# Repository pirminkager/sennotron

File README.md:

# sennotron-beeromat

Sennotron is also a great beer brewer!

Read out adc is working
Data collection and saving (data.py) is working

## Installation

It is important to always have a stable and predictive environment. Packages installed on the system
could interfere with packages installed for this project. In addition it makes it easier to install this project
on different systems.

    # create a virtual python environment based on python3.
    # all packages installed with pip will be installed under this location
    virtualenv --python=python3 .venv3

    # apply/source the environment
    # this command needs to be repeated whenever a new shell is opened
    source .venv3/bin/python

    # install project dependencies
    pip install -r requirements.txt

## Todo

### main.py + controls
### mpc.py
### model.py
### error estimation?
### alert.py?
### display.py

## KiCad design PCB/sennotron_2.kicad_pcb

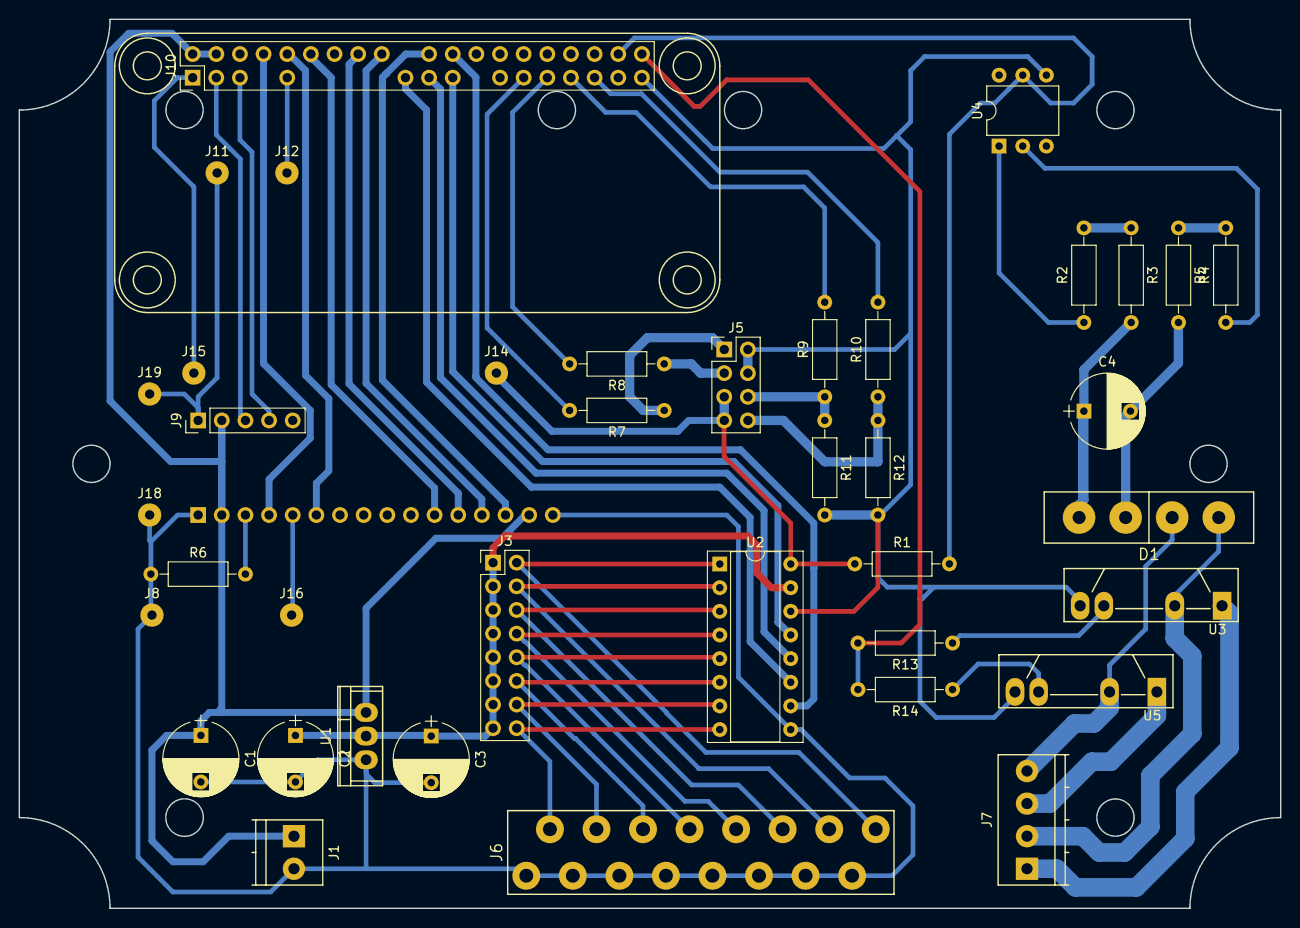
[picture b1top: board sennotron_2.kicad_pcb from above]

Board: 4 copper layers, 135.5 x 95.5 mm, 40 parts (1 on the bottom side), 47 nets.

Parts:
C1, C3: CP; CP_Radial_D8.0mm_P5.00mm
C2: 22µF/50V; CP_Radial_D8.0mm_P5.00mm
C4: C; CP_Radial_D8.0mm_P5.00mm
D1: D_Bridge_+-AA; SIP-4
J1: Screw_Terminal_01x02; TerminalBlock_Phoenix_PT-3.5mm_2pol
J3: Conn_02x08_Odd_Even; Pin_Header_Straight_2x08_Pitch2.54mm
J4: Conn_01x16_Female; Pin_Header_Straight_1x16_Pitch2.54mm
J5: Conn_02x04_Odd_Even; Pin_Header_Straight_2x04_Pitch2.54mm
J6: Screw_Terminal_01x16; springlock
J7: Screw_Terminal_01x04; TerminalBlock_Phoenix_PT-3.5mm_4pol
J8, J11, J12, J14, J15, J16, J18, J19: Conn_01x01; Pad_2.5
J9: Conn_01x05_Female; Socket_Strip_Straight_1x05_Pitch2.54mm
J10: Conn_02x20_Odd_Even; raspberry_pi_zero
R1, R2, R3, R4, R5, R6, R7, R8, R9, R10, R11, R12, R13, R14: R; R_Axial_DIN0207_L6.3mm_D2.5mm_P10.16mm_Horizontal
U1: LM1117-3.3; TO-220
U2: MCP3208; DIP-16_W7.62mm_Socket
U3, U5: S102S01; SIP4_Sharp-SSR_Pitch7.62mm_Straight
U4: 4N28; DIP-6_W7.62mm

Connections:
+3.3VA: C2.1, C3.1, J3.1, J3.3, J3.5, J3.7, J3.9, J3.11, J3.13, J3.15, U1.2, U2.15
+3V3: J5.5, J5.7, J10.1, J14.1, J15.1, R1.1, U2.16
+5V: C1.1, J1.1, J4.2, J4.15, J9.2, J10.2, J10.4, U1.3
/btn1: J10.33, R9.2
/btn2: J10.35, R10.2
/led1: J10.29, R7.2
/led2: J10.31, R8.2
AC_sens: J10.38, R1.2, U4.5
GND: C1.2, C2.2, C3.2, J1.2, J4.1, J4.5, J4.16, J5.2, J5.4, J6.1, J6.3, J6.5, J6.7, J6.9, J6.11, J6.13, J6.15, J8.1, J9.1, J10.9, J10.39, J11.1, J12.1, J16.1, J18.1, J19.1, R6.1, R11.2, R12.2, U1.1, U2.9, U2.14, U3.4, U4.4, U5.4
unnamed: C4.1, D1.1, R3.2
unnamed: C4.2, D1.2, R5.2
unnamed: D1.3, J7.4, U5.2
unnamed: D1.4, J7.2, U3.2
unnamed: J3.2, J6.16, U2.1
unnamed: J3.4, J6.14, U2.2
unnamed: J3.6, J6.12, U2.3
unnamed: J3.8, J6.10, U2.4
unnamed: J3.10, J6.8, U2.5
unnamed: J3.12, J6.6, U2.6
unnamed: J3.14, J6.4, U2.7
unnamed: J3.16, J6.2, U2.8
unnamed: J4.3, R6.2
unnamed: J5.1, R7.1
unnamed: J5.3, R8.1
unnamed: J5.6, R9.1, R11.1
unnamed: J5.8, R10.1, R12.1
unnamed: J7.1, U3.1
unnamed: J7.3, U5.1
unnamed: R2.1, U4.1
unnamed: R2.2, R3.1
unnamed: R4.1, U4.2
unnamed: R4.2, R5.1
unnamed: R13.1, U3.3
unnamed: R14.1, U5.3
heat_trig: J10.40, R13.2, R14.2
lcd_d4: J4.11, J10.12
lcd_d5: J4.12, J10.16
lcd_d6: J4.13, J10.18
lcd_d7: J4.14, J10.22
lcd_en: J4.6, J10.10
lcd_rs: J4.4, J10.8
scl: J9.4, J10.5
sda: J9.3, J10.3
spi_clk: J10.23, U2.13
spi_cs_0: J10.24, U2.10
spi_miso: J10.21, U2.12
spi_mosi: J10.19, U2.11

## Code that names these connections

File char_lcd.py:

#!/usr/bin/python
import time

import Adafruit_CharLCD as LCD

from datetime import datetime

# Raspberry Pi pin configuration:
lcd_rs        = 25
lcd_en        = 24
lcd_d4        = 23
lcd_d5        = 17
lcd_d6        = 18
lcd_d7        = 22
lcd_backlight = 27

# Define LCD column and row size for 16x2 LCD.
lcd_columns = 16
lcd_rows    = 2

# Initialize the LCD using the pins above.
lcd = LCD.Adafruit_CharLCD(lcd_rs, lcd_en, lcd_d4, lcd_d5, lcd_d6, lcd_d7,
                           lcd_columns, lcd_rows, lcd_backlight)



#Test Section
if __name__ == '__main__':
    # Print a two line message
    lcd.message('Hello\nworld!')

    # Wait 5 seconds
    time.sleep(1.0)

    # Demo showing the cursor.
    lcd.clear()
    lcd.show_cursor(True)
    lcd.message('Show cursor')

    time.sleep(1.0)

    # Demo showing the blinking cursor.
    lcd.clear()
    lcd.blink(True)
    lcd.message('Blink cursor')

    time.sleep(1.0)

    # Stop blinking and showing cursor.
    lcd.show_cursor(False)
    lcd.blink(False)

    # Demo scrolling message right/left.
    lcd.clear()
    message = 'Scroll'
    lcd.message(message)
    for i in range(lcd_columns-len(message)):
        time.sleep(0.1)
        lcd.move_right()
    for i in range(lcd_columns-len(message)):
        time.sleep(0.1)
        lcd.move_left()

    # Demo turning backlight off and on.
    lcd.clear()
    lcd.message('Flash backlight\nin 5 seconds...')
    time.sleep(1.0)
    # Turn backlight off.
    lcd.set_backlight(0)
    time.sleep(1.0)
    # Change message.
    lcd.clear()
    lcd.message('Goodbye!')
    # Turn backlight on.
    lcd.set_backlight(1)
    lcd.clear()


    while 1:
        lcd.clear()
        lcd.message(str(time.time())+'\n')
        lcd.message(datetime.now().strftime('%b %d  %H:%M:%S\n'))
        time.sleep(1)

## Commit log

2018-05-10 Add model and ADC.py
2018-05-10 added char_lcd lib
2018-05-10 add gitignore and ignore compiled python files *.pyc.
    They should not be part of the repository.
2018-05-10 And remove compiled file.
2018-05-10 add python requirements file to track package dependencies.
2018-05-10 added class for datacollection and manipulation in data.py
2018-05-10 Mention virtualenv in README.
2018-05-10 Add an example class.
2018-05-10 put the virtualenv directory to the git ignore list.
2018-05-10 Put the goals into the README
2018-05-10 remove goals file. Is in the README now.
    It is nicer to be read on github.
2018-05-12 display module has now 3 functions to fill display with a text, a value for temperature and the remaining time
2018-05-12 extra_requirements
    where do these requirements go?
2018-05-13 cleanup repo
2018-05-17 parser included
2018-05-20 some work done with model.py but no working predicting algorithm yet
2018-05-20 There it is... ready to be designed!
2018-05-23 Schematics and PCB design updated
2018-05-23 gitignore updated
2018-05-23 no message
2018-05-25 ...
    Redesigned the pcb. Some Additions in the .sch. Moved the new pcb to "_2"
2018-05-28 pcb design almost done... waiting for a review!
